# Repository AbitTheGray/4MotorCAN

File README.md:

# 3D Printer 4-Motor Board (CAN-bus Device)

This is a hobby project to create 3D Printer board to allow either control of all 4 motors (XYZ + Extruder) or 4 motors per axis.

The brain is [RP2040](https://www.raspberrypi.com/products/rp2040/) (can be flashed using USB-C connector) and has [TMC5160](https://www.trinamic.com/products/integrated-circuits/details/tmc5160/) as its muscle.
All the power and commands are provided by [CAN bus](https://en.wikipedia.org/wiki/CAN_bus) [Molex Micro-Fit 3.0 connector](https://www.molex.com/en-us/products/connectors/wire-to-board-connectors/micro-fit-connectors).
If you do not want to use CAN bus, you must provide 24V and GND on the connector and connect USB-C to your controller.

I have tried putting as many notes into the schematic as possible.
Buck converters and LDOs have their voltage limits close to the input pins (those are recommended limits, not absolute ones).

*[Molex Micro-Fit 3.0](https://www.molex.com/en-us/products/connectors/wire-to-board-connectors/micro-fit-connectors) connectors are on the preview shown as 2x03 2.54mm/0.1" Pin Socket due to a missing 3D model.

## Features

- [CAN bus](https://en.wikipedia.org/wiki/CAN_bus) with power
  - 24V + 48V passthrough (48V optional, choose correct fuse orientation)
  - 5V signal
- 4x [TMC5160](https://www.trinamic.com/products/integrated-circuits/details/tmc5160/) to control motors (slotted PCB)
  - Encoder connector
  - Step LED (shows every step of the motor)
  - Optional direction switched (input, see TMC5160 documentation)
- 4x Limit Switch (endstop)
- RGB header (5V but signal is 3.3V)
- 4x 2pin Temperature sensor (resistor)
- 4x 2pin Fan control (5V / 12V / 24V) with 250mA fuse
- 2x Heating enable ("trigger", cannot power the heating)

### Warnings
- **This project was not yet tested. Use at your own risk.**
- This project uses RP2040 as if it was a 5V microcontroller.
  RP2040 is not officially 5V-tolerant but is reported by users to be able to process 5V input.
  And 3V output is 60% of 5V which should be enough for HIGH digital value of 5V devices.
- There is no overvoltage protection, do not turn axis motors too fast (manually)
  - Fan connectors have over-current protection (resettable fuse) in case of short circuit, but it will stop them from working
- Each motor has 3A max (total 12A) but [Molex Micro-Fit 3.0 connector](https://www.molex.com/en-us/products/connectors/wire-to-board-connectors/micro-fit-connectors) is rated only for 8.5A / 10.5A (depending on your source-of-truth) leaving only 2.125A / 2.625A per motor
    - This current limit is for the whole [CAN bus](https://en.wikipedia.org/wiki/CAN_bus)! The limit is least-rated connector in the network
    - [JST XH connectors](https://www.jst.com/products/crimp-style-connectors-wire-to-board-type/xh-connector/) should not esceed 3A.
- You should not power any heating through [CAN bus](https://en.wikipedia.org/wiki/CAN_bus) as power consumption can exceed safe limits for those connectors (and wires).

Keep in mind any current/temperature limits can be lower for higher-temperature environments (like fully boxed-in 3D printer).

## Limits and Power Consumption

| Component                | Expected Max Current | Max Temperature |
|--------------------------|----------------------|-----------------|
| RP2040 (microcontroller) | 50 mA                | 85 °C           |
| W25Q128JVS (flash)       | 4 mA                 | 85 °C (105 °C)  |
| TMC5160 (motor driver)   |                      | 125 °C          |
| Stepper motor            | 3A (x4)              |                 |

## Usage

Following usages are all theoretical based on hardware capabilities, none have been tested.

In case you do not want to use the 3mm pitch Molex connector for power, you can use the 3 pads in top-left corner to solder your wires directly to the PCB.
This is not recommended as it will usually skip fuse for motors (unless you use 24V for motors using `F103`).

### 3D Printer Board

This board can be used as a main 3D printer board as it has everything required for a basic printer (4 motors, limit switches, temperature sensors, heating triggers).

### CAN/USB Device

This device can be controlled using either [CAN bus](https://en.wikipedia.org/wiki/CAN_bus) or USB.
Having 4 motors and several input/output connectors, you can control most/all of the 3D printer from single CAN device.
In case of multiple motors per axis, you may need multiple devices (this board was primarily designed to control 4 Z-axis motors using single controller over CAN).

## Fabrication

DNP (Do Not Place/Populate) symbols are also removed from "Component Position" output.
The same applies to all connectors as those are not recommended/possible for automatic soldering.

You can save some money by replacing `R602`+`D601` by `R601` (and equivalent for `R701`,`R801` and `R901`) and omitting `R101`-`R105` and `D101`-`D105` (power indication LEDs).

### Problems

- No equivalent for `C201`/`C202` currently available
- No THT connectors in Component Placement files
  - 10x 2pin JST XH
  - 5x 3pin JST XH
  - 4x 4pin JST XH
  - 4x 5pin JST XH
  - 2x [Molex Micro-Fit 3.0 connector](https://www.molex.com/en-us/products/connectors/wire-to-board-connectors/micro-fit-connectors)
  - 2x12 2.54cm/0.1" Pin Header
  - 4x 4pin 2.54cm/0.1" Pin Header
  - 8x 8pin 2.54cm/0.1" Pin Header

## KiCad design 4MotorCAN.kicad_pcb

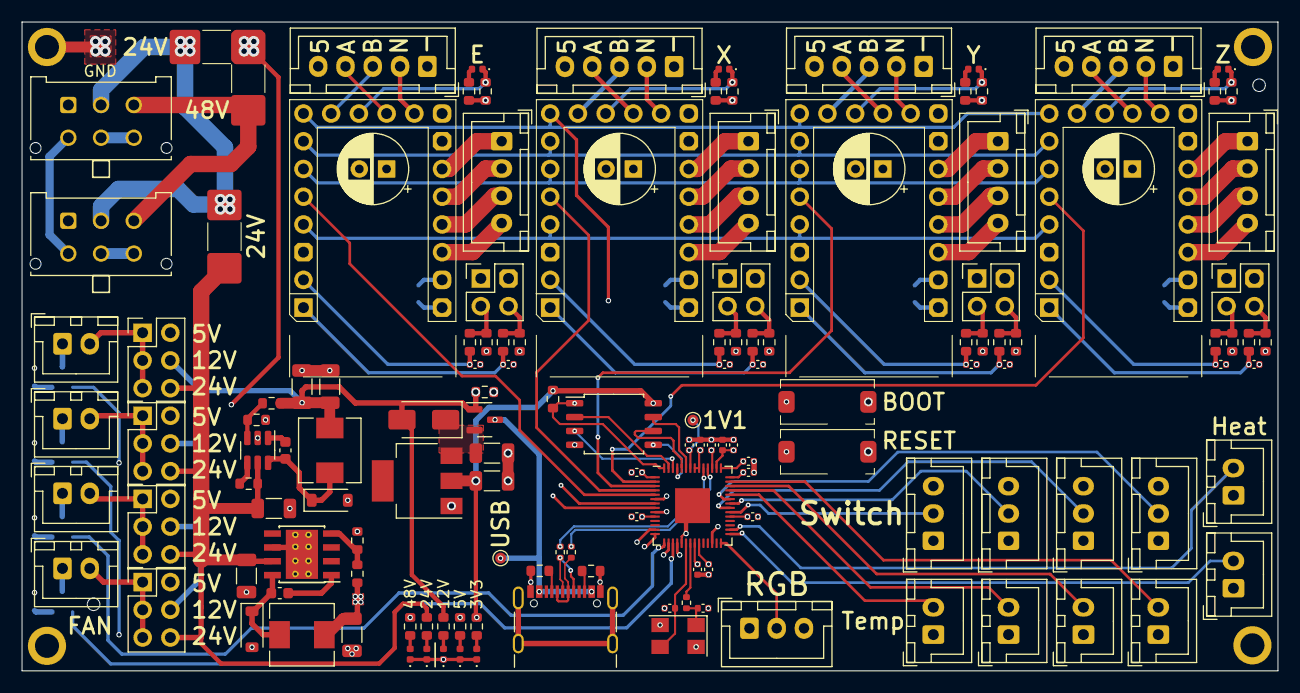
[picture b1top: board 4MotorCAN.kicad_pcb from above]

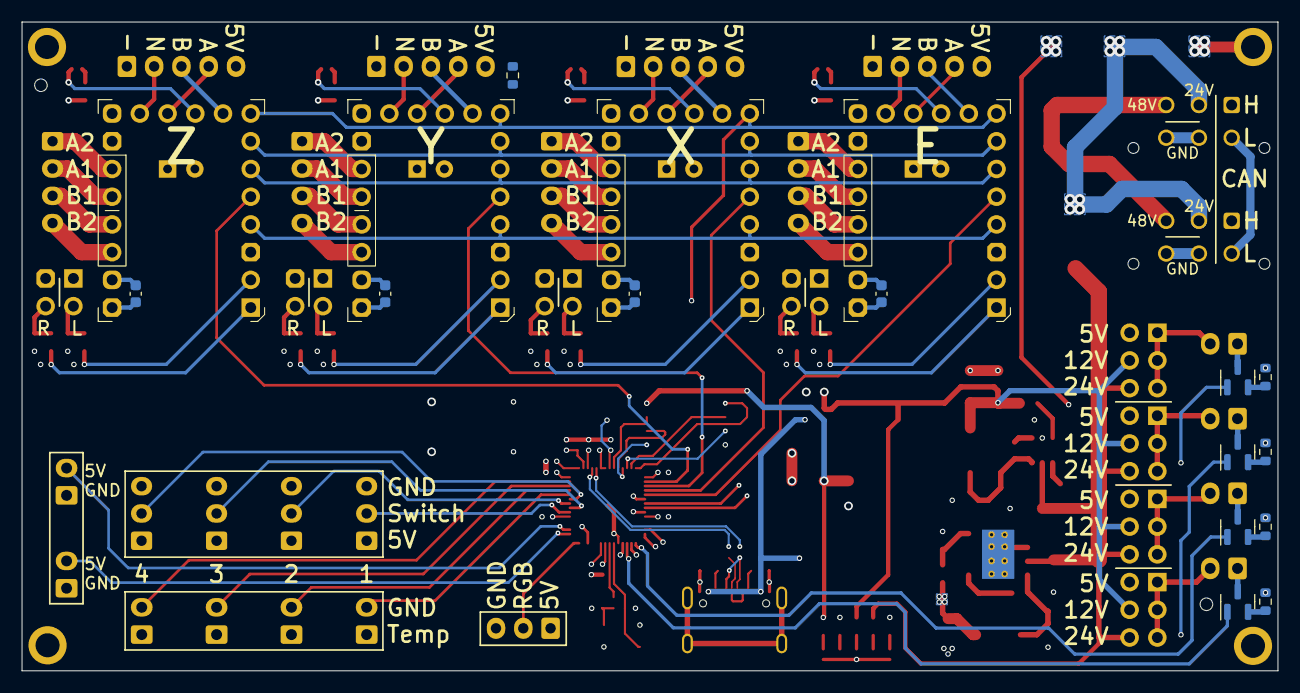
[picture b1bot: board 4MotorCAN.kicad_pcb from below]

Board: 6 copper layers, 115.1 x 59.4 mm, 161 parts (13 on the bottom side), 128 nets.

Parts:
C201, C202: 14pF; C_0402_1005Metric
C211, C231, C232, C233, C234, C235, C236, C237, C238, C239, C611, C612, C711, C712, C811, C812, C911, C912: 100nF; C_0402_1005Metric
C221, C222: 1uF; C_0402_1005Metric
C301, C302, C311, C313, C321, C323, C324: 10uF; C_1206_3216Metric
C312, C322: 10nF; C_0603_1608Metric
C601, C701, C801, C901: 470nF; C_0603_1608Metric
C602, C702, C802, C902: ???; CP_Radial_D6.3mm_P2.50mm
D101, D102, D103, D104, D105, D601, D701, D801, D901: White; LED_0402_1005Metric
D301: D_Schottky; D_SMA
D311, D321: B5819W; D_SOD-123
F101, F102, F103: 65V 20A; Fuse_2410_6125Metric
F401, F402, F403, F404: 250mA; R_0603_1608Metric
H101, H102, H103, H104: MountingHole_Pad; MountingHole_2.2mm_M2_ISO7380_Pad
H111, H112: MountingHole_Pad; Tooling Hole (JLCPCB)
J101, J102: Molex Micro-Fit 3.0 2x03 - CAN bus; Molex_Micro-Fit_3.0_43045-0612_2x03_P3.00mm_Vertical
J111: RGB; JST_XH_B3B-XH-A_1x03_P2.50mm_Vertical
J121, J122, J123, J124: Temperature; JST_XH_B2B-XH-A_1x02_P2.50mm_Vertical
J131, J132: Heating Enable; JST_XH_B2B-XH-A_1x02_P2.50mm_Vertical
J141, J142, J143, J144: Limit Switch; JST_XH_B3B-XH-A_1x03_P2.50mm_Vertical
J301: USB_C_Receptacle_USB2.0; USB_C_Receptacle_GCT_USB4105-xx-A_16P_TopMnt_Horizontal
J401, J403, J405, J407: Fan Connector; JST_XH_B2B-XH-A_1x02_P2.50mm_Vertical
J402, J404, J406, J408: Fan Voltage Selection; PinHeader_2x03_P2.54mm_Vertical
J601, J701, J801, J901: Motor Connector; JST_XH_B4B-XH-A_1x04_P2.50mm_Vertical
J602, J702, J802, J902: Encoder; JST_XH_B5B-XH-A_1x05_P2.50mm_Vertical
J603, J703, J803, J903: Direction; PinHeader_2x02_P2.54mm_Vertical
L311, L321: 10uH; L_Sunlord_MWSA0503S
Q301: Si2309CDS; SOT-23
Q401, Q402, Q403, Q404: BSS138; SOT-23
R101: 90k; R_0603_1608Metric
R102: 42k; R_0603_1608Metric
R103: 18k; R_0603_1608Metric
R104, R602, R702, R802, R902: 4.7k; R_0603_1608Metric
R105: 600; R_0603_1608Metric
R201: 1k; R_0402_1005Metric
R211, R212: 27.4R; R_0402_1005Metric
R221, R301, R311, R501, R611, R613, R711, R713, R811, R813, R911, R913: 10k; R_0603_1608Metric
R312: 3.2k; R_0603_1608Metric
R321: 100k; R_0603_1608Metric
R322, R601, R612, R614, R701, R712, R714, R801, R812, R814, R901, R912, R914: 47k; R_0603_1608Metric
R323: 3.4k; R_0603_1608Metric
R331, R332: 5.1k; R_0603_1608Metric
SW201: Reset; Button 6x3.6mm
SW202: Boot; Button 6x3.6mm
TP101, TP107: TestPoint; TestPoint_Pad_D1.0mm
U201: RP2040; QFN-56-1EP_7x7mm_P0.4mm_EP3.2x3.2mm
U202: W25Q128JVS; SOIC-8_5.23x5.23mm_P1.27mm
U301: AMS1117-3.3; SOT-223-3_TabPin2
U311: TPS5430DDA; TI_SO-PowerPAD-8_ThermalVias
U321: MP2359DJ; SOT-23-6
U601, U701, U801, U901: FYSETC TMC5160
Y201: 12MHz; Crystal_SMD_5032-4Pin_5.0x3.2mm

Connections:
+1V1: C221.1, C231.1, C232.1, TP101.1, U201.23 (DVDD), U201.45 (VREG_VOUT), U201.50 (DVDD)
+3V3: C211.1, C222.1, C233.1, C234.1, C235.1, C236.1, C237.1, C238.1, C239.1, C302.1, R105.2, R221.1, U201.1 (IOVDD), U201.10 (IOVDD), U201.22 (IOVDD), U201.33 (IOVDD), U201.42 (IOVDD), U201.43 (ADC_AVDD), U201.44 (VREG_IN), U201.48 (USB_VDD), U201.49 (IOVDD), U202.8 (VCC), U301.2 (VO)
+5V: C313.1, C601.1, C701.1, C801.1, C901.1, J111.1, J141.1, J142.1, J143.1, J144.1, J402.2, J404.2, J406.2, J408.2, J602.5, J702.5, J802.5, J902.5, L311.2, R104.2, R311.1, R501.2, R601.2, R602.2, R611.2, R613.2, R701.2, R702.2, R711.2, R713.2, R801.2, R802.2, R811.2, R813.2, R901.2, R902.2, R911.2, R913.2, U601.19 (VIO), U701.19 (VIO), U801.19 (VIO), U901.19 (VIO)
+12V: C323.1, C324.1, D301.2 (A), J402.4, J404.4, J406.4, J408.4, L321.2, Q301.1 (G), R103.2, R301.2, R322.1
+24V: C311.1, C321.1, F101.2, J402.6, J404.6, J406.6, J408.6, R102.2, R321.1, U311.7 (VIN), U321.5 (IN)
+48V: C602.1, C702.1, C802.1, C902.1, F102.2, F103.2, R101.2, U601.13 (VM), U701.13 (VM), U801.13 (VM), U901.13 (VM)
/CAN 24V: F101.1, F103.1, J101.2, J102.2
/CAN 48V: F102.1, J101.3, J102.3
/Microcontroller/QSPI_SCLK: U201.52 (QSPI_SCLK), U202.6 (CLK)
/Microcontroller/QSPI_SD0: U201.53 (QSPI_SD0), U202.5 (DI(IO0))
/Microcontroller/QSPI_SD1: U201.55 (QSPI_SD1), U202.2 (DO(IO1))
/Microcontroller/QSPI_SD2: U201.54 (QSPI_SD2), U202.3 (IO2)
/Microcontroller/QSPI_SD3: U201.51 (QSPI_SD3), U202.7 (IO3)
/Microcontroller/QSPI_SS: R221.2, SW202.2, U201.56 (QSPI_SS), U202.1 (~CS)
/Microcontroller/RUN: SW201.2, U201.26 (RUN)
/Microcontroller/XIN: C201.1, U201.20 (XIN), Y201.3
/Microcontroller/XOUT: C202.1, R201.1, Y201.1
/Motor Drivers/Motor 1/M1_A1: J601.2, U601.16 (A1)
/Motor Drivers/Motor 1/M1_A2: J601.1, U601.15 (A2)
/Motor Drivers/Motor 1/M1_B1: J601.3, U601.17 (B1)
/Motor Drivers/Motor 1/M1_B2: J601.4, U601.18 (B2)
/Motor Drivers/Motor 1/M1_ENC_A: J602.4, U601.11 (ENC-A)
/Motor Drivers/Motor 1/M1_ENC_B: J602.3, U601.9 (ENC-B)
/Motor Drivers/Motor 1/M1_ENC_N: J602.2, U601.12 (ENC-N)
/Motor Drivers/Motor 2/M2_A1: J701.2, U701.16 (A1)
/Motor Drivers/Motor 2/M2_A2: J701.1, U701.15 (A2)
/Motor Drivers/Motor 2/M2_B1: J701.3, U701.17 (B1)
/Motor Drivers/Motor 2/M2_B2: J701.4, U701.18 (B2)
/Motor Drivers/Motor 2/M2_ENC_A: J702.4, U701.11 (ENC-A)
/Motor Drivers/Motor 2/M2_ENC_B: J702.3, U701.9 (ENC-B)
/Motor Drivers/Motor 2/M2_ENC_N: J702.2, U701.12 (ENC-N)
/Motor Drivers/Motor 3/M3_A1: J801.2, U801.16 (A1)
/Motor Drivers/Motor 3/M3_A2: J801.1, U801.15 (A2)
/Motor Drivers/Motor 3/M3_B1: J801.3, U801.17 (B1)
/Motor Drivers/Motor 3/M3_B2: J801.4, U801.18 (B2)
/Motor Drivers/Motor 3/M3_ENC_A: J802.4, U801.11 (ENC-A)
/Motor Drivers/Motor 3/M3_ENC_B: J802.3, U801.9 (ENC-B)
/Motor Drivers/Motor 3/M3_ENC_N: J802.2, U801.12 (ENC-N)
/Motor Drivers/Motor 4/M4_A1: J901.2, U901.16 (A1)
/Motor Drivers/Motor 4/M4_A2: J901.1, U901.15 (A2)
/Motor Drivers/Motor 4/M4_B1: J901.3, U901.17 (B1)
/Motor Drivers/Motor 4/M4_B2: J901.4, U901.18 (B2)
/Motor Drivers/Motor 4/M4_ENC_A: J902.4, U901.11 (ENC-A)
/Motor Drivers/Motor 4/M4_ENC_B: J902.3, U901.9 (ENC-B)
/Motor Drivers/Motor 4/M4_ENC_N: J902.2, U901.12 (ENC-N)
/Power Supply/CC1: J301.A5 (CC1), R331.1
/Power Supply/CC2: J301.B5 (CC2), R332.1
/Power Supply/VIN: C301.1, D301.1 (K), Q301.2 (S), U301.3 (VI)
Bed Heating: J131.2, U201.29 (GPIO18)
CAN-H: J101.1, J102.1, U201.14 (GPIO11)
CAN-L: J101.4, J102.4, U201.13 (GPIO10)
FAN1: Q401.1 (G), U201.18 (GPIO15)
FAN2: Q402.1 (G), U201.16 (GPIO13)
FAN3: Q403.1 (G), U201.15 (GPIO12)
FAN4: Q404.1 (G), U201.17 (GPIO14)
GND: C201.2, C202.2, C211.2, C221.2, C222.2, C231.2, C232.2, C233.2, C234.2, C235.2, C236.2, C237.2, C238.2, C239.2, C301.2, C302.2, C311.2, C313.2, C321.2, C323.2, C324.2, C601.2, C602.2, C611.2, C612.2, C701.2, C702.2, C711.2, C712.2, C801.2, C802.2, C811.2, C812.2, C901.2, C902.2, C911.2, C912.2, D101.1 (K), D102.1 (K), D103.1 (K), D104.1 (K), D105.1 (K), D311.2 (A), D321.2 (A), F401.2, F402.2, F403.2, F404.2, H101.1, H102.1, H103.1, H104.1, J101.5, J101.6, J102.5, J102.6, J111.3, J121.1, J122.1, J123.1, J124.1, J131.1, J132.1, J141.3, J142.3, J143.3, J144.3, J301.A1 (GND), J301.A12 (GND), J301.B1 (GND), J301.B12 (GND), J602.1, J603.1, J603.2, J702.1, J703.1, J703.2, J802.1, J803.1, J803.2, J902.1, J903.1, J903.2, R301.1, R312.2, R323.2, R331.2, R332.2, SW201.1, SW202.1, U201.19 (TESTEN), U201.57 (GND), U202.4 (GND), U301.1 (GND), U311.6 (GND), U311.9 (GNDPAD), U321.2 (GND), U601.3 (CLK), U601.14 (GND), U601.20 (GND), U701.3 (CLK), U701.14 (GND), U701.20 (GND), U801.3 (CLK), U801.14 (GND), U801.20 (GND), U901.3 (CLK), U901.14 (GND), U901.20 (GND), Y201.2, Y201.4
Head Heating: J132.2, U201.30 (GPIO19)
Limit 1: J141.2, U201.34 (GPIO22)
Limit 2: J142.2, U201.36 (GPIO24)
Limit 3: J143.2, U201.35 (GPIO23)
Limit 4: J144.2, U201.37 (GPIO25)
M1 OUT STEP: D601.1 (K), R601.1, U601.10 (DIAG0)
M1 REF L: C611.1, R612.1, U601.2 (STEP)
M1 REF R: C612.1, R614.1, U601.1 (DIR)
M2 OUT STEP: D701.1 (K), R701.1, U701.10 (DIAG0)
M2 REF L: C711.1, R712.1, U701.2 (STEP)
M2 REF R: C712.1, R714.1, U701.1 (DIR)
M3 OUT STEP: D801.1 (K), R801.1, U801.10 (DIAG0)
M3 REF L: C811.1, R812.1, U801.2 (STEP)
M3 REF R: C812.1, R814.1, U801.1 (DIR)
M4 OUT STEP: D901.1 (K), R901.1, U901.10 (DIAG0)
M4 REF L: C911.1, R912.1, U901.2 (STEP)
M4 REF R: C912.1, R914.1, U901.1 (DIR)
unnamed: D101.2 (A), R101.1
unnamed: D102.2 (A), R102.1
unnamed: D103.2 (A), R103.1
unnamed: D104.2 (A), R104.1
unnamed: D105.2 (A), R105.1
unnamed: C312.1, D311.1 (K), L311.1, U311.8 (PH)
unnamed: C322.1, D321.1 (K), L321.1, U321.6 (Switch)
unnamed: D601.2 (A), R602.1
unnamed: D701.2 (A), R702.1
unnamed: D801.2 (A), R802.1
unnamed: D901.2 (A), R902.1
unnamed: J401.1, Q401.3 (D)
unnamed: J401.2, J402.1, J402.3, J402.5
unnamed: J403.1, Q402.3 (D)
unnamed: J403.2, J404.1, J404.3, J404.5
unnamed: J405.1, Q403.3 (D)
unnamed: J405.2, J406.1, J406.3, J406.5
unnamed: J407.1, Q404.3 (D)
unnamed: J407.2, J408.1, J408.3, J408.5
unnamed: J603.3, R611.1, R612.2
unnamed: J603.4, R613.1, R614.2
unnamed: J703.3, R711.1, R712.2
unnamed: J703.4, R713.1, R714.2
unnamed: J803.3, R811.1, R812.2
unnamed: J803.4, R813.1, R814.2
unnamed: J903.3, R911.1, R912.2
unnamed: J903.4, R913.1, R914.2
unnamed: F401.1, Q401.2 (S)
unnamed: F402.1, Q402.2 (S)
unnamed: F403.1, Q403.2 (S)
unnamed: F404.1, Q404.2 (S)
unnamed: R212.2, U201.46 (USB_DM)
unnamed: R211.2, U201.47 (USB_DP)
unnamed: R201.2, U201.21 (XOUT)
unnamed: C312.2, U311.1 (BOOT)
unnamed: R311.2, R312.1, U311.4 (VSENSE)
unnamed: C322.2, U321.1 (Boost)
unnamed: R321.2, U321.4 (EN)
unnamed: R322.2, R323.1, U321.3 (Feedback)
RGB: J111.2, U201.28 (GPIO17)
SPI CLK: U201.8 (GPIO6), U601.6 (SCK), U701.6 (SCK), U801.6 (SCK), U901.6 (SCK)
SPI MISO: U201.6 (GPIO4), U601.4 (SDO), U701.4 (SDO), U801.4 (SDO), U901.4 (SDO)
SPI MOSI: U201.7 (GPIO5), U601.7 (SDI), U701.7 (SDI), U801.7 (SDI), U901.7 (SDI)
SPI ~CS M1: U201.5 (GPIO3), U601.5 (CS)
SPI ~CS M2: U201.4 (GPIO2), U701.5 (CS)
SPI ~CS M3: U201.3 (GPIO1), U801.5 (CS)
SPI ~CS M4: U201.2 (GPIO0), U901.5 (CS)
Temp 1: J121.2, U201.38 (GPIO26_ADC0)
Temp 2: J122.2, U201.39 (GPIO27_ADC1)
Temp 3: J123.2, U201.40 (GPIO28_ADC2)
Temp 4: J124.2, U201.41 (GPIO29_ADC3)
USB D+: J301.A6 (D+), J301.B6 (D+), R211.1
USB D-: J301.A7 (D-), J301.B7 (D-), R212.1
VUSB: J301.A4 (VBUS), J301.A9 (VBUS), J301.B4 (VBUS), J301.B9 (VBUS), Q301.3 (D), TP107.1
~MOTOR ENABLE: R501.1, U201.9 (GPIO7), U601.8 (EN), U701.8 (EN), U801.8 (EN), U901.8 (EN)

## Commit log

2023-08-18 Initial raw draft
2023-08-19 Assigning a lot of values to components Change MOSFETS for different (correct) ones Copy Motor1 to Motor2-4 Guess max current per voltage on PowerSupply schema
2023-08-19 Complete schematics Assign every value (very few exceptions) Change TCM5160 from on-board to separate module Add fuses Add power supplies (LDO + 2x buck converter)
2023-08-19 WIP PCB placement, minor fixes
2023-08-19 More PCB placement, fix 48V for Motors
2023-08-22 Finish wiring PCB
2023-08-22 CC-BY-SA 4.0
2023-08-27 Finish PCB, documentation
